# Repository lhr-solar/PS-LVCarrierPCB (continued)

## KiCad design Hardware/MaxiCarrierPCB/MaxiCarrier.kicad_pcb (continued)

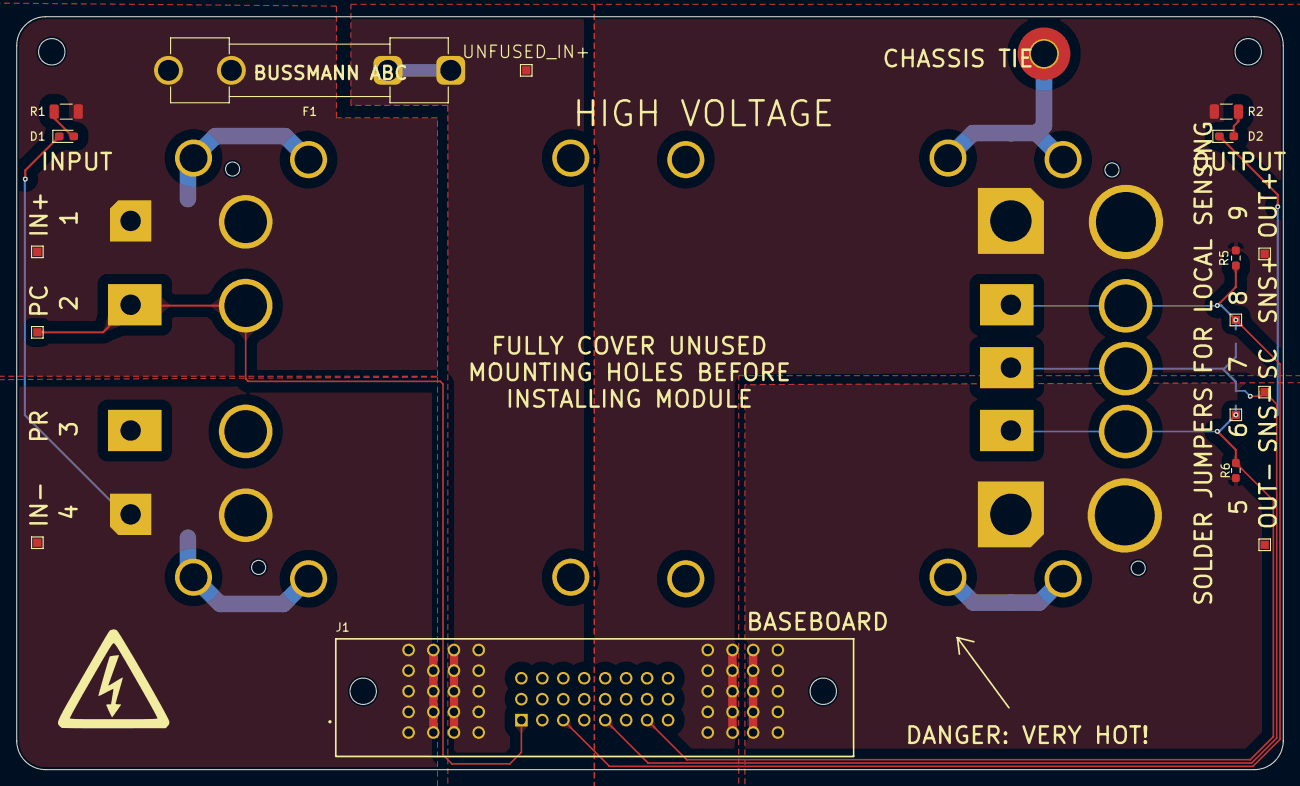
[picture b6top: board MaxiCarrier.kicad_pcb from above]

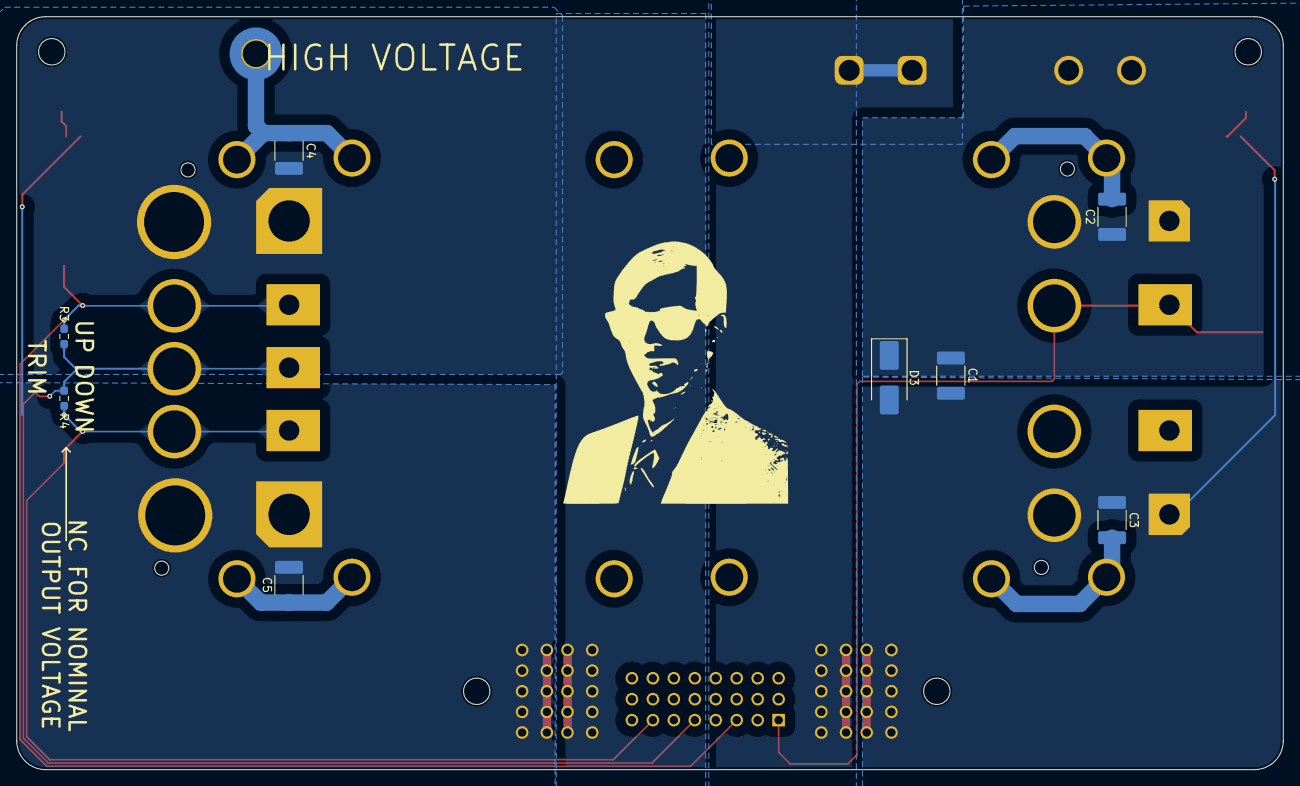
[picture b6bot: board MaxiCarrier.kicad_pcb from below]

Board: 2 copper layers, 153.5 x 91.2 mm, 31 parts (9 on the bottom side), 12 nets.

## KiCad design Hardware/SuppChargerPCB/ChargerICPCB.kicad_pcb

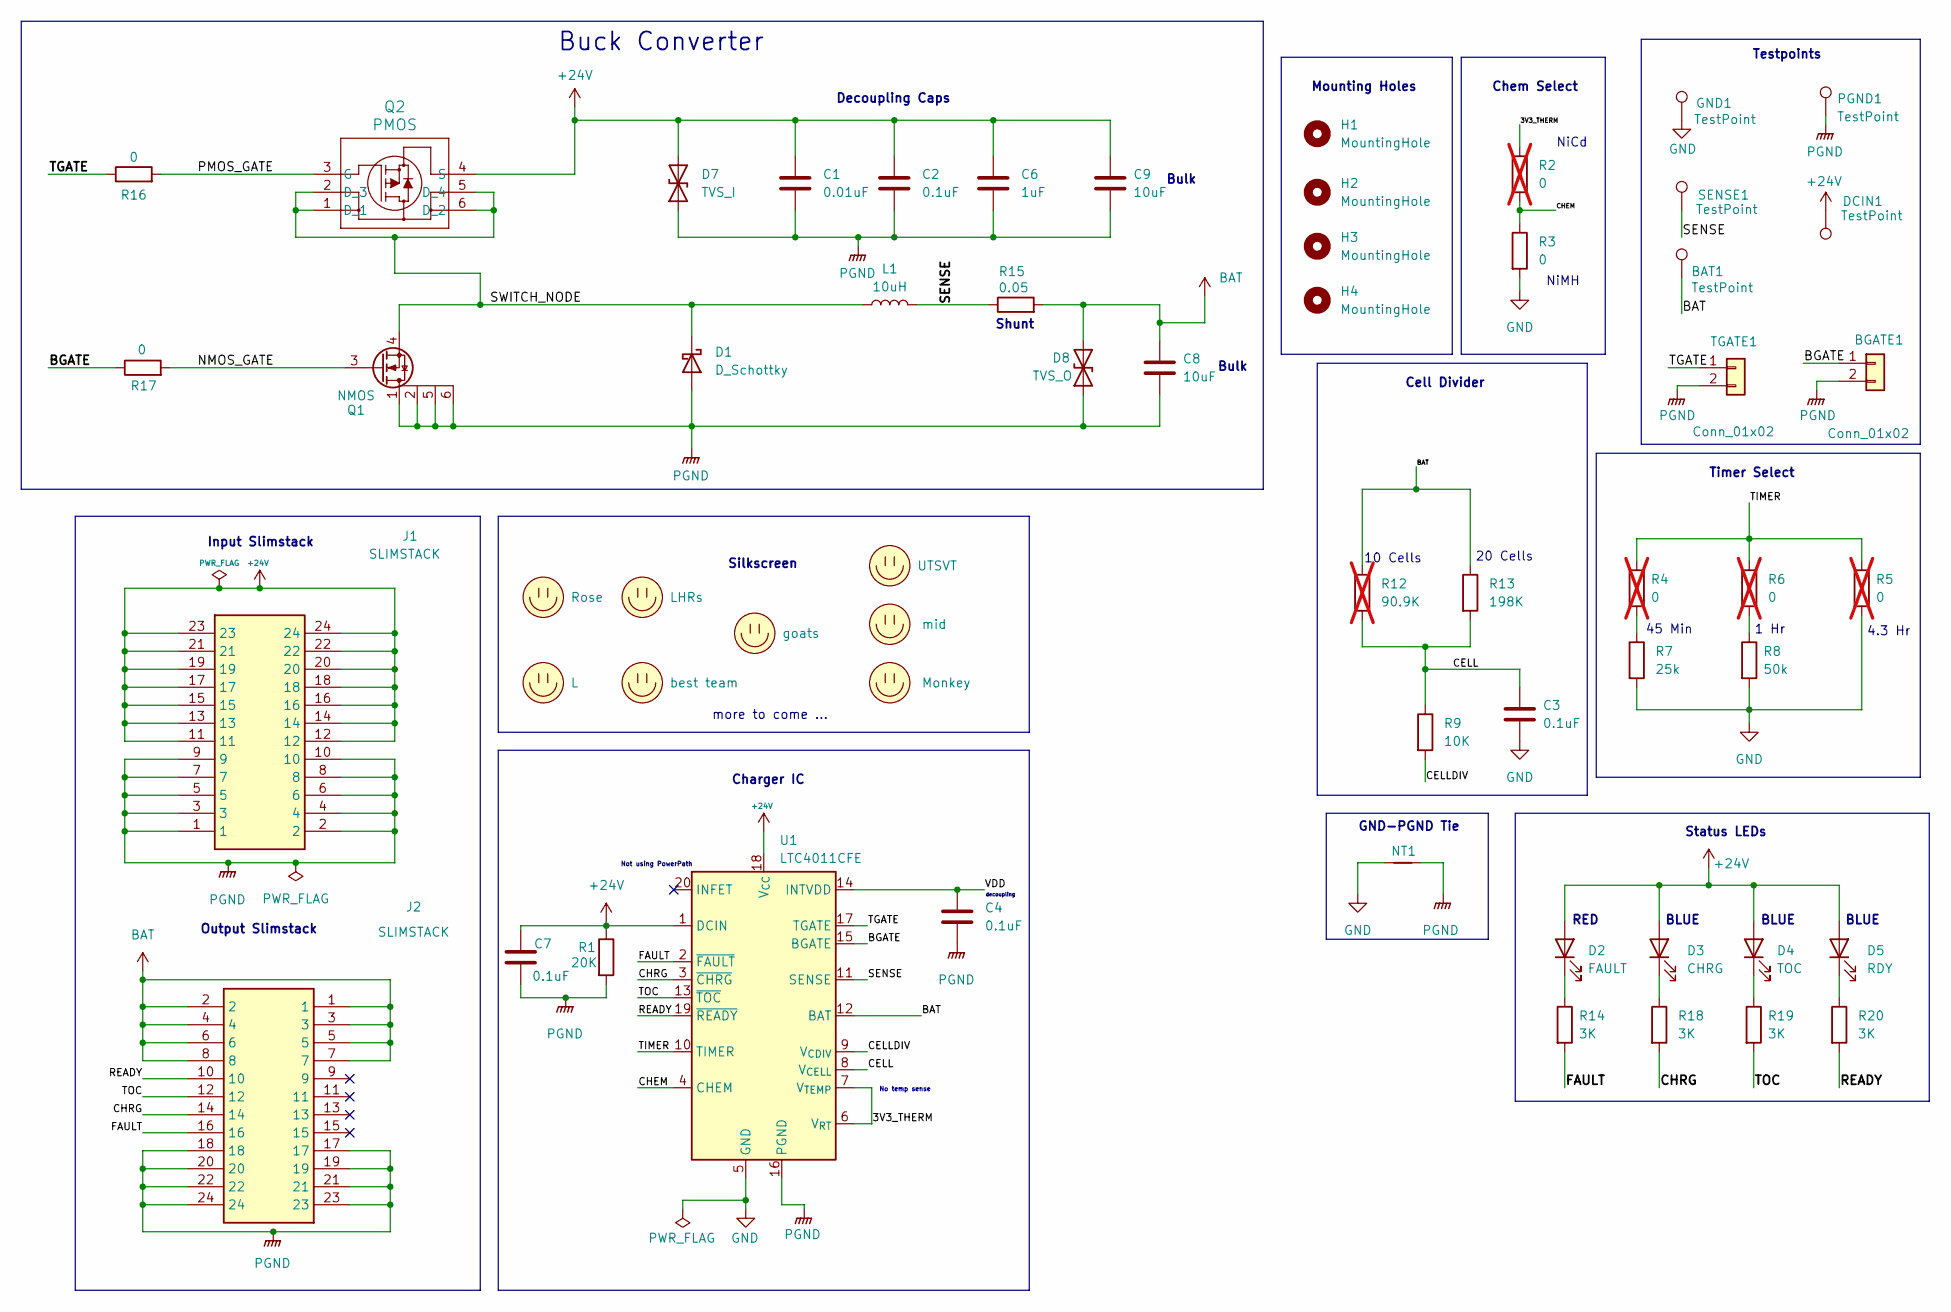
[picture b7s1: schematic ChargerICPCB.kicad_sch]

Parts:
BAT1: TestPoint; PinHeader_1x01_P2.54mm_Vertical
BGATE1: Conn_01x02; PinHeader_1x02_P2.54mm_Vertical
C1: 0.01uF; C_0603_1608Metric
C2, C3, C4, C7: 0.1uF; C_0603_1608Metric
C6: 1uF; C_0603_1608Metric
C8, C9: 10uF; C_0805_2012Metric
D1: D_Schottky; UPS140E3TR7
D2: FAULT; C_0603_1608Metric
D3: CHRG; LED_0603_1608Metric
D4: TOC; LED_0603_1608Metric
D5: RDY; LED_0603_1608Metric
D7: TVS_I; D_SMB
D8: TVS_O; D_SMB
DCIN1: TestPoint; PinHeader_1x01_P2.54mm_Vertical
GND1: TestPoint; PinHeader_1x01_P2.54mm_Vertical
H1, H2, H3, H4: MountingHole; MountingHole_3.2mm_M3
J1, J2: SLIMSTACK; 524652470; Mouser Part Number 538-52465-2470
L1: 10uH; WE-LHMI_7050
LOGO1: LHRs; LHRs_LOGO
LOGO2: UTSVT; UTSVT_Logo_Symbol
LOGO3: Monkey; monk
LOGO5: Rose; rose
LOGO6: L
LOGO7: best team; sunderland
LOGO8: goats; chinese
LOGO9: mid
NT1: NetTie_2; NetTie-2_SMD_Pad0.5mm
PGND1: TestPoint; PinHeader_1x01_P2.54mm_Vertical
Q1: NMOS; TSOP6_MO-193C_VIS; Mouser Part Number Si3456DDV
Q2: PMOS; TSOT23-6-419BL_OSI
R1: 20K; R_0603_1608Metric
R2, R4, R5, R6: 0; R_0603_1608Metric; not fitted
R3, R16, R17: 0; R_0603_1608Metric
R7: 25k; R_0603_1608Metric
R8: 50k; R_0603_1608Metric
R9: 10K; R_0603_1608Metric
R12: 90.9K; R_0603_1608Metric_Pad0.98x0.95mm_HandSolder; not fitted
R13: 198K; R_0603_1608Metric_Pad0.98x0.95mm_HandSolder
R14, R18, R19, R20: 3K; R_0603_1608Metric
R15: 0.05; R_0603_1608Metric
SENSE1: TestPoint; PinHeader_1x01_P2.54mm_Vertical
TGATE1: Conn_01x02; PinHeader_1x02_P2.54mm_Vertical
U1: LTC4011CFE; HTSSOP-20-1EP_4.4x6.5mm_P0.65mm_EP2.74x3.86mm

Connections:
+24V: C1.1, C2.1, C6.1, C7.1, C9.1, D2.2 (A), D3.2 (A), D4.2 (A), D5.2 (A), D7.2 (A2), DCIN1.1, J1.11, J1.12, J1.13, J1.14, J1.15, J1.16, J1.17, J1.18, J1.19, J1.20, J1.21, J1.22, J1.23, J1.24, Q2.4 (S), R1.1, U1.1 (DCIN), U1.18 (V_{CC})
/3V3_THERM: R2.1, U1.6 (V_{RT}), U1.7 (V_{TEMP})
/BGATE: BGATE1.1, R17.1, U1.15 (BGATE)
/CELL: C3.1, R9.1, R12.2, R13.2, U1.8 (V_{CELL})
/CELLDIV: R9.2, U1.9 (V_{CDIV})
/CHEM: R2.2, R3.1, U1.4 (CHEM)
/CHRG: J2.14, R18.2, U1.3 (~CHRG)
/FAULT: J2.16, R14.2, U1.2 (~FAULT)
/NMOS_GATE: Q1.3 (G), R17.2
/PMOS_GATE: Q2.3 (G), R16.2
/READY: J2.10, R20.2, U1.19 (~READY)
/SENSE: L1.2, R15.1, SENSE1.1, U1.11 (SENSE)
/SWITCH_NODE: D1.1 (K), L1.1, Q1.4 (S), Q2.1 (D_1), Q2.2 (D_3), Q2.5 (D_4), Q2.6 (D_2)
/TGATE: R16.1, TGATE1.1, U1.17 (TGATE)
/TIMER: R4.1, R5.1, R6.1, U1.10 (TIMER)
/TOC: J2.12, R19.2, U1.13 (~TOC)
/VDD: C4.1, U1.14 (INTVDD)
BAT: BAT1.1, C8.1, D8.2 (A2), J2.1, J2.2, J2.3, J2.4, J2.5, J2.6, J2.7, J2.8, R12.1, R13.1, R15.2, U1.12 (BAT)
GND: C3.2, GND1.1, NT1.1, R3.2, R5.2, R7.2, R8.2, U1.5 (GND), U1.21 (GND)
unnamed: D2.1 (K), R14.1
unnamed: D3.1 (K), R18.1
unnamed: D4.1 (K), R19.1
unnamed: D5.1 (K), R20.1
unnamed: R4.2, R7.1
unnamed: R6.2, R8.1
PGND: BGATE1.2, C1.2, C2.2, C4.2, C6.2, C7.2, C8.2, C9.2, D1.2 (A), D7.1 (A1), D8.1 (A1), J1.1, J1.2, J1.3, J1.4, J1.5, J1.6, J1.7, J1.8, J1.9, J1.10, J2.17, J2.18, J2.19, J2.20, J2.21, J2.22, J2.23, J2.24, NT1.2, PGND1.1, Q1.1 (D), Q1.2 (S), Q1.5 (S), Q1.6 (S), R1.2, TGATE1.2, U1.16 (PGND)

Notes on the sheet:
10 Cells
Shunt
4.3 Hr
decoupling
BLUE
RED
Status LEDs
Not using PowerPath
Silkscreen
Testpoints
GND-PGND Tie
Mounting Holes
Decoupling Caps
45 Min
Timer Select
Output Slimstack
more to come ...
20 Cells
Charger IC
No temp sense
Bulk
Cell Divider
NiMH
Buck Converter
NiCd
Input Slimstack
1 Hr
Chem Select

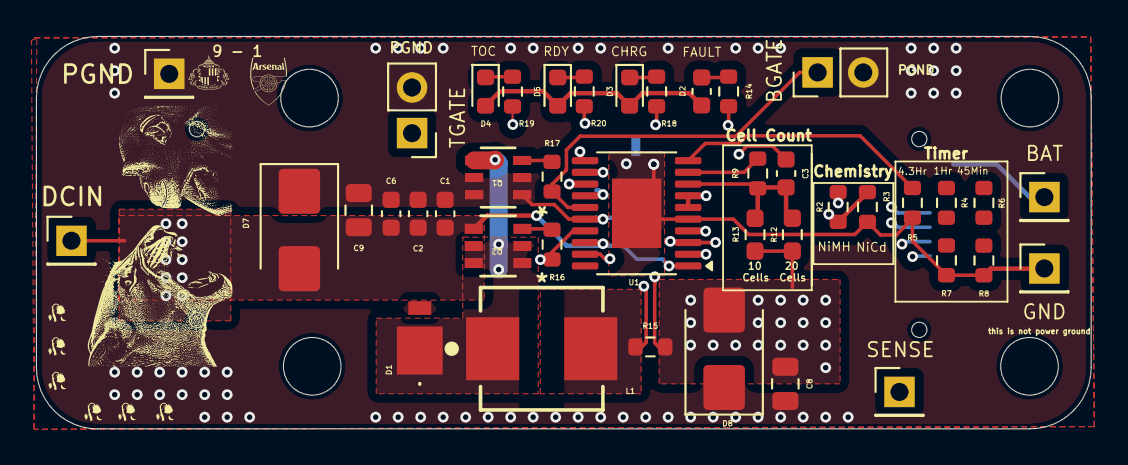
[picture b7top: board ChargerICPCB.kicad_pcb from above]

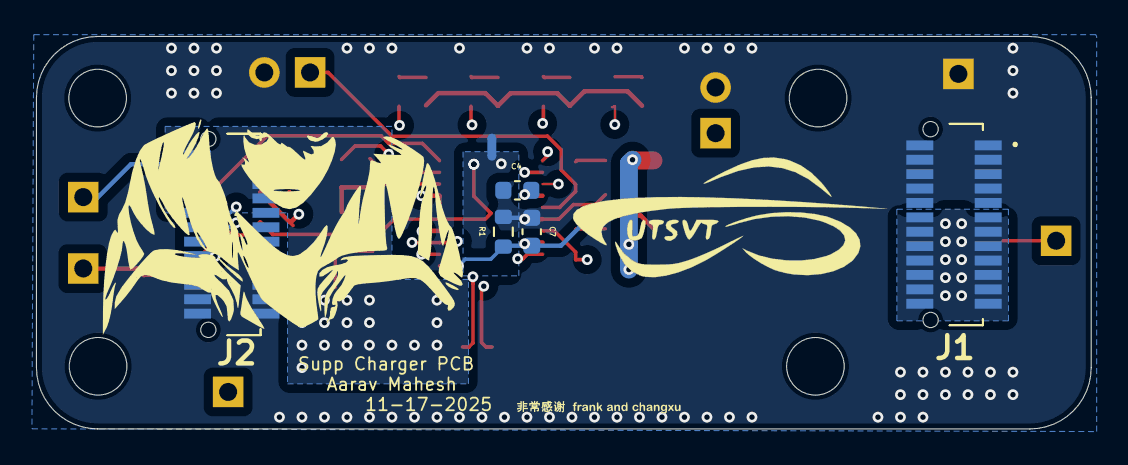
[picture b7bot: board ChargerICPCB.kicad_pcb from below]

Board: 4 copper layers, 58.6 x 21.8 mm, 64 parts (10 on the bottom side), 26 nets.

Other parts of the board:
LOGO5#2, LOGO5#3, LOGO5#4, LOGO5#5, LOGO5#6: Rose; rose

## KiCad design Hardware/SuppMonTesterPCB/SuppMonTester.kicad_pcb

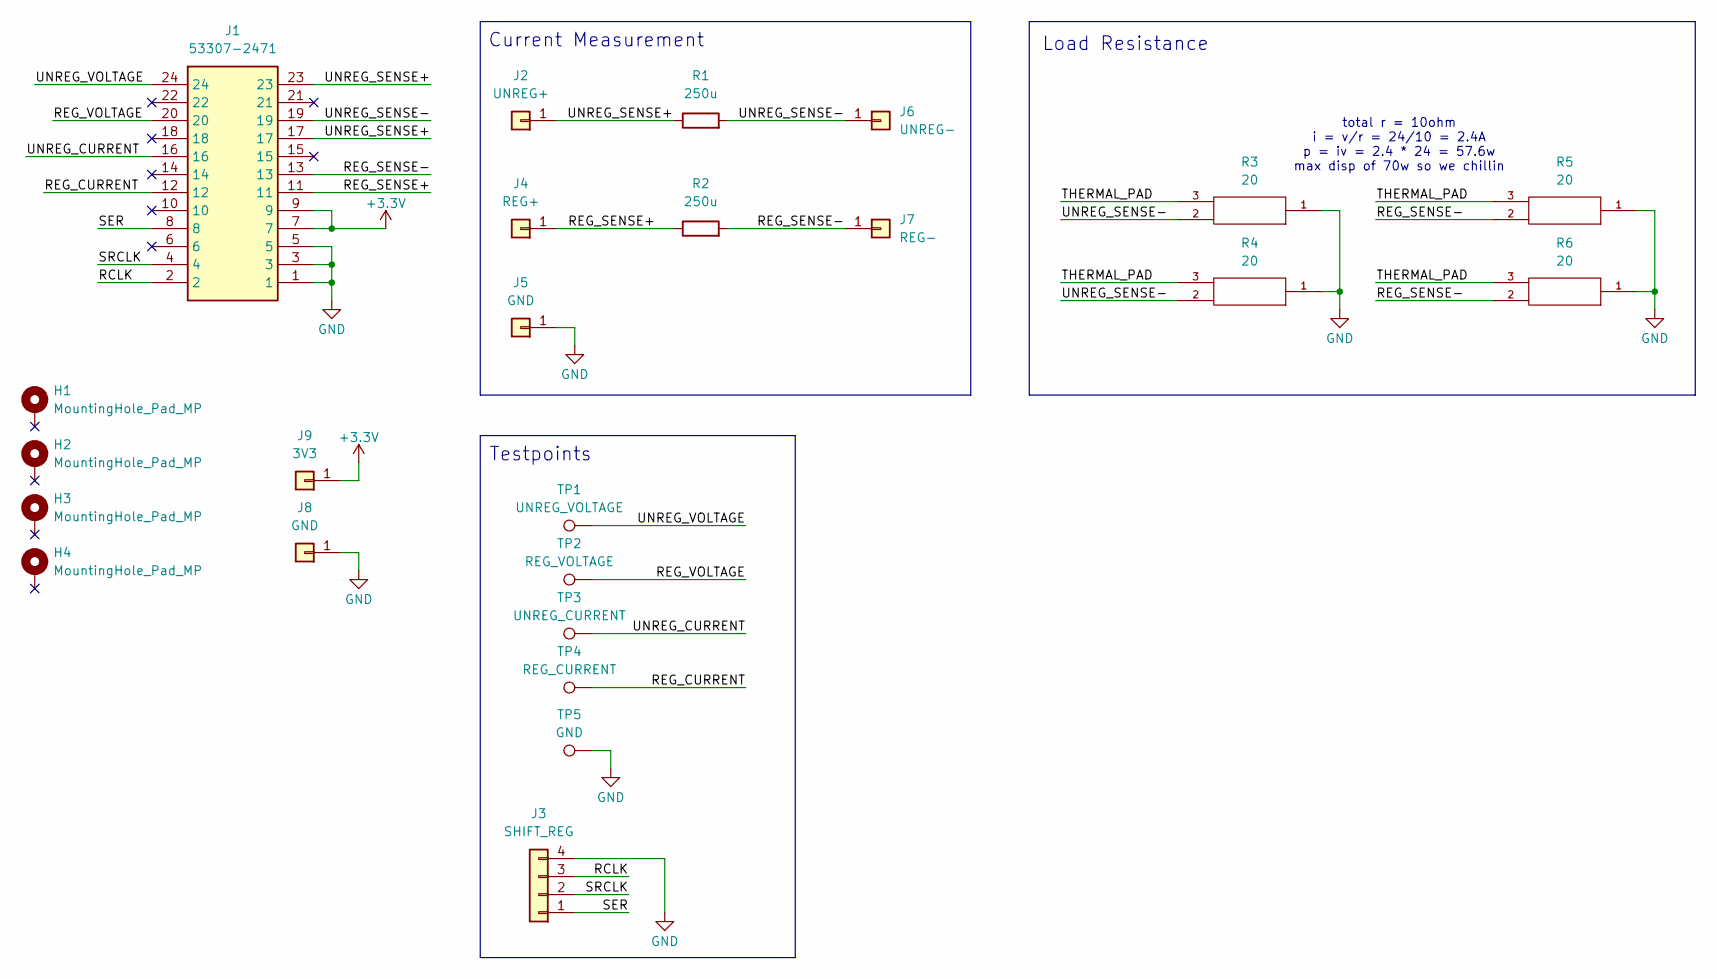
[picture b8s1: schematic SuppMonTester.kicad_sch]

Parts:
H1, H2, H3, H4: MountingHole_Pad_MP; MountingHole_3.2mm_M3_Pad
J1: 53307-2471; 533072471; Mouser Part Number 538-53307-2471
J2: UNREG+; 5754
J3: SHIFT_REG; PinHeader_1x04_P2.54mm_Vertical
J4: REG+; 5754
J5, J8: GND; 5754
J6: UNREG-; 5754
J7: REG-; 5754
J9: 3V3; 5754
R1, R2: 250u; R_1225_3264Metric_Pad1.47x6.45mm_HandSolder
R3, R4, R5, R6: 20; RES_PWR263S-35-3300F; PARTREV 12/20
TP1: UNREG_VOLTAGE; TestPoint_HEX_3mmID
TP2: REG_VOLTAGE; TestPoint_HEX_3mmID
TP3: UNREG_CURRENT; TestPoint_HEX_3mmID
TP4: REG_CURRENT; TestPoint_HEX_3mmID
TP5: GND; TestPoint_HEX_3mmID

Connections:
+3.3V: J1.7, J1.9, J9.1
/RCLK: J1.2, J3.3
/REG_CURRENT: J1.12, TP4.1
/REG_SENSE+: J1.11, J4.1, R2.1
/REG_SENSE-: J1.13, J7.1, R2.2, R5.2, R6.2
/REG_VOLTAGE: J1.20, TP2.1
/SER: J1.8, J3.1
/SRCLK: J1.4, J3.2
/THERMAL_PAD: R3.3, R4.3, R5.3, R6.3
/UNREG_CURRENT: J1.16, TP3.1
/UNREG_SENSE+: J1.17, J1.23, J2.1, R1.1
/UNREG_SENSE-: J1.19, J6.1, R1.2, R3.2, R4.2
/UNREG_VOLTAGE: J1.24, TP1.1
GND: J1.1, J1.3, J1.5, J3.4, J5.1, J8.1, R3.1, R4.1, R5.1, R6.1, TP5.1

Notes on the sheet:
total r = 10ohm i = v/r = 24/10 = 2.4A p = iv = 2.4 * 24 = 57.6w max disp of 70w so we chillin
Load Resistance
Current Measurement
Testpoints

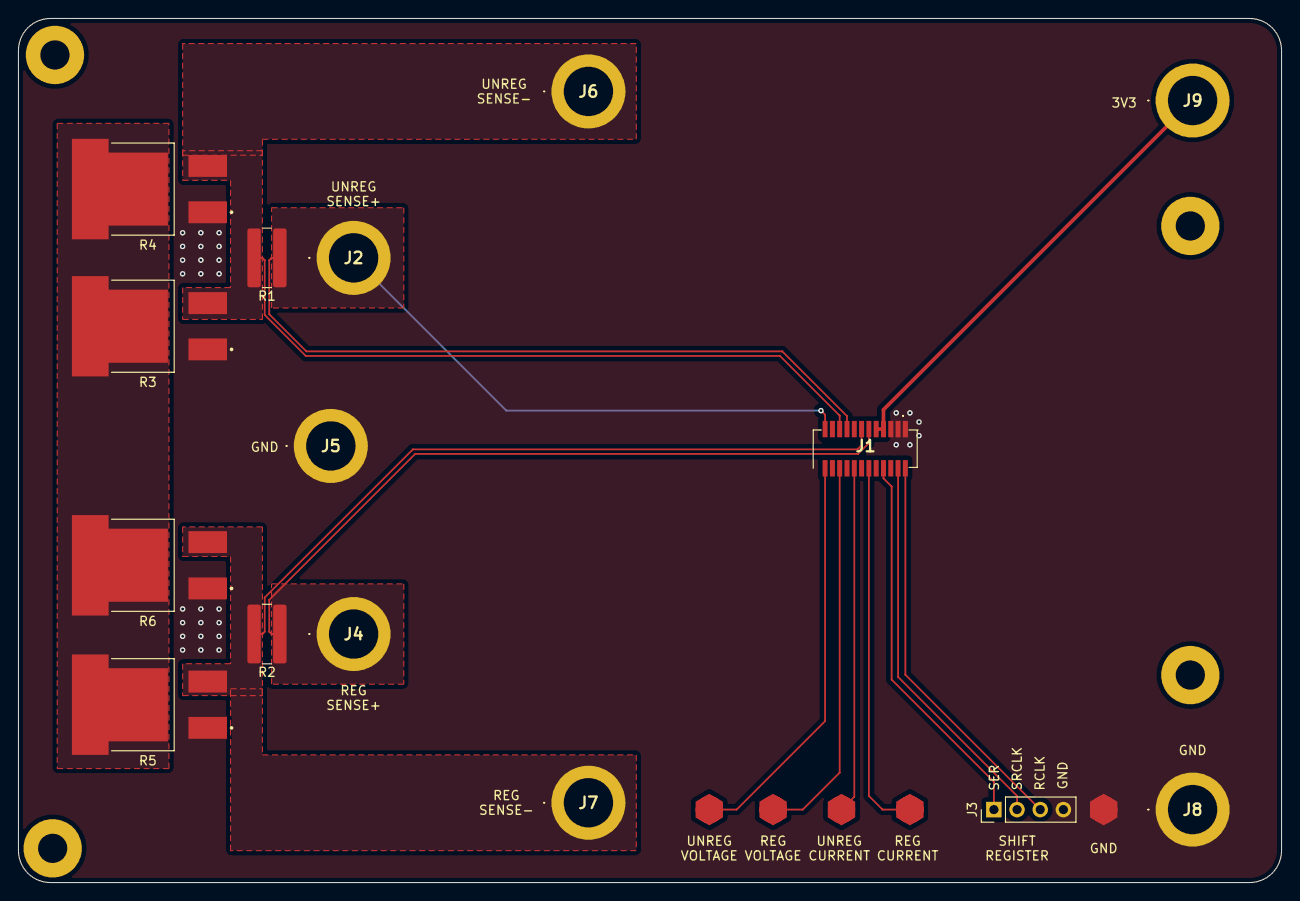
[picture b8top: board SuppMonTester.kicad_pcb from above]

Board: 2 copper layers, 138.5 x 94.8 mm, 24 parts (0 on the bottom side), 14 nets.

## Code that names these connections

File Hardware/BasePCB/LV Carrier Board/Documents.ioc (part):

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Mcu.Name=STM32G473R(B-C-E)Tx
Mcu.Package=LQFP64
Mcu.UserName=STM32G473RETx
PA0.GPIOParameters=GPIO_Label
PA0.GPIO_Label=R_Current
PA0.Mode=IN1-Single-Ended
PA0.Signal=ADC1_IN1
PA1.GPIOParameters=GPIO_Label
PA1.GPIO_Label=L_Current
PA1.Mode=IN2-Single-Ended
PA1.Signal=ADC2_IN2
PA10.GPIOParameters=GPIO_Label
PA10.GPIO_Label=UVR1
PA10.Signal=GPIO_Input
PA11.GPIOParameters=GPIO_Label
PA11.GPIO_Label=UVF2
PA11.Signal=GPIO_Input
PA12.GPIOParameters=GPIO_Label
PA12.GPIO_Label=UVF1
PA12.Signal=GPIO_Input
PA13.Mode=Serial_Wire
PA13.Signal=SYS_JTMS-SWDIO
PA14.Mode=Serial_Wire
PA14.Signal=SYS_JTCK-SWCLK
PA15.GPIOParameters=GPIO_Label
PA15.GPIO_Label=CANH
PA15.Mode=FDCAN_Activate
PA15.Signal=FDCAN3_TX
PA2.GPIOParameters=GPIO_Label
PA2.GPIO_Label=R_Voltage
PA2.Mode=IN3-Differential
PA2.Signal=ADC1_IN3
PA3.GPIOParameters=GPIO_Label
PA3.GPIO_Label=L_Voltage
PA3.Mode=IN3-Differential
PA3.Signal=ADC1_IN4
PA4.GPIOParameters=GPIO_Label
PA4.GPIO_Label=SD Card
PA4.Mode=NSS_Signal_Hard_Output
PA4.Signal=SPI1_NSS
PA5.GPIOParameters=GPIO_Label
PA5.GPIO_Label=SD Card
PA5.Mode=Full_Duplex_Master
PA5.Signal=SPI1_SCK
PA6.GPIOParameters=GPIO_Label
PA6.GPIO_Label=SD Card
PA6.Mode=Full_Duplex_Master
PA6.Signal=SPI1_MISO
PA7.GPIOParameters=GPIO_Label
PA7.GPIO_Label=SD Card
PA7.Mode=Full_Duplex_Master
PA7.Signal=SPI1_MOSI
PA8.GPIOParameters=GPIO_Label
PA8.GPIO_Label=CANL
PA8.Mode=FDCAN_Activate
PA8.Signal=FDCAN3_RX
PA9.GPIOParameters=GPIO_Label
PA9.GPIO_Label=SD Card Detect
PA9.Signal=GPIO_Input
PB0.GPIOParameters=GPIO_Label
PB0.GPIO_Label=CH1
PB0.Signal=GPIO_Input
PB1.GPIOParameters=GPIO_Label
PB1.GPIO_Label=L_Shunt
PB1.Mode=IN12-Single-Ended
PB1.Signal=ADC1_IN12
PB10.GPIOParameters=GPIO_Label
PB10.GPIO_Label=UVR2
PB10.Signal=GPIO_Input
PB11.GPIOParameters=GPIO_Label
PB11.GPIO_Label=SUPP V out
PB11.Signal=GPIO_Input
PB12.GPIOParameters=GPIO_Label
PB12.GPIO_Label=VALID2
PB12.Signal=GPIO_Input
PB13.GPIOParameters=GPIO_Label
PB13.GPIO_Label=FTL2
PB13.Signal=GPIO_Output
PB14.GPIOParameters=GPIO_Label
PB14.GPIO_Label=FTL1
PB14.Signal=GPIO_Output
PB15.GPIOParameters=GPIO_Label
PB15.GPIO_Label=CHL2
PB15.Signal=GPIO_Output
PB2.GPIOParameters=GPIO_Label
PB2.GPIO_Label=FAULT1
PB2.Signal=GPIO_Input
PB3.GPIOParameters=GPIO_Label
PB3.GPIO_Label=OV1
PB3.Signal=GPIO_Input
PB4.GPIOParameters=GPIO_Label
PB4.GPIO_Label=STATUS_LED
PB4.Mode=PWM Generation2 CH2N
PB4.Signal=TIM8_CH2N
PB5.GPIOParameters=GPIO_Label
PB5.GPIO_Label=SR_CLK
PB5.Signal=S_TIM17_CH1
PB6.Signal=S_TIM8_CH1
PB7.GPIOParameters=GPIO_Label
PB7.GPIO_Label=BOOT Switch
PB7.Signal=GPIO_Input
PB8-BOOT0.GPIOParameters=GPIO_Label
PB8-BOOT0.GPIO_Label=BootSwitch
PB8-BOOT0.Signal=GPIO_Input
PB9.GPIOParameters=GPIO_Label
PB9.GPIO_Label=SR_Data
PB9.Signal=GPIO_Input
PC0.GPIOParameters=GPIO_Label
PC0.GPIO_Label=R_Input
PC0.Mode=IN6-Differential
PC0.Signal=ADC1_IN6
PC1.GPIOParameters=GPIO_Label
PC1.GPIO_Label=L_Input
PC1.Mode=IN6-Differential
PC1.Signal=ADC1_IN7
PC10.GPIOParameters=GPIO_Label
PC10.GPIO_Label=Supp V Out
PC10.Signal=GPIO_Input
PC11.GPIOParameters=GPIO_Label
PC11.GPIO_Label=DISABLE2
PC11.Signal=GPIO_Input
PC12.GPIOParameters=GPIO_Label
PC12.GPIO_Label=VALID1
PC12.Signal=GPIO_Input
PC13.GPIOParameters=GPIO_Label
PC13.GPIO_Label=CH1
PC13.Signal=GPIO_Input
PC14-OSC32_IN.GPIOParameters=GPIO_Label
PC14-OSC32_IN.GPIO_Label=FAULT2
PC14-OSC32_IN.Signal=GPIO_Input
PC15-OSC32_OUT.GPIOParameters=GPIO_Label
PC15-OSC32_OUT.GPIO_Label=CH2
PC15-OSC32_OUT.Signal=GPIO_Input
PC2.GPIOParameters=GPIO_Label
PC2.GPIO_Label=R_Shunt
PC2.Mode=IN8-Differential
PC2.Signal=ADC1_IN8
PC3.GPIOParameters=GPIO_Label
PC3.GPIO_Label=IMON
PC3.Mode=IN8-Differential
PC3.Signal=ADC1_IN9
PC4.Mode=Asynchronous
PC4.Signal=USART1_TX
PC5.Mode=Asynchronous
PC5.Signal=USART1_RX
PC6.GPIOParameters=GPIO_Label
PC6.GPIO_Label=CHL1
PC6.Signal=GPIO_Output
PC7.GPIOParameters=GPIO_Label
PC7.GPIO_Label=VDL2
PC7.Signal=GPIO_Output
PC8.GPIOParameters=GPIO_Label
PC8.GPIO_Label=VDL1
PC8.Signal=GPIO_Output
PC9.GPIOParameters=GPIO_Label
PC9.GPIO_Label=OV2
PC9.Signal=GPIO_Input
PD2.GPIOParameters=GPIO_Label
PD2.GPIO_Label=DISABLE1
PD2.Signal=GPIO_Input
PF0-OSC_IN.GPIOParameters=GPIO_Label
PF0-OSC_IN.GPIO_Label=Crystal
PF0-OSC_IN.Mode=HSE-External-Oscillator
PF0-OSC_IN.Signal=RCC_OSC_IN
PF1-OSC_OUT.GPIOParameters=GPIO_Label
PF1-OSC_OUT.GPIO_Label=Crystal
PF1-OSC_OUT.Mode=HSE-External-Oscillator
PF1-OSC_OUT.Signal=RCC_OSC_OUT
PG10-NRST.GPIOParameters=GPIO_Label
PG10-NRST.GPIO_Label=Reset Button
PG10-NRST.Signal=GPIO_Input
RCC.HSE_VALUE=8000000
RCC.SYSCLKFreq_VALUE=16000000
board=custom

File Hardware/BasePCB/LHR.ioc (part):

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Mcu.Name=STM32G473R(B-C-E)Tx
Mcu.Package=LQFP64
Mcu.UserName=STM32G473RETx
PA0.GPIOParameters=GPIO_Label
PA0.GPIO_Label=SUPPMON_V2
PA0.Signal=ADC1_IN1
PA1.GPIOParameters=GPIO_Label
PA1.GPIO_Label=SUPPMON_V1
PA1.Mode=IN2-Differential
PA1.Signal=ADC1_IN2
PA10.GPIOParameters=GPIO_Label
PA10.GPIO_Label=SR_CLK
PA10.Signal=S_TIM1_CH3
PA13.Signal=SYS_JTMS-SWDIO
PA14.Signal=SYS_JTCK-SWCLK
PA15.GPIOParameters=GPIO_Label
PA15.GPIO_Label=CAN_H
PA15.Mode=FDCAN_Activate
PA15.Signal=FDCAN3_TX
PA2.GPIOParameters=GPIO_Label
PA2.GPIO_Label=SUPPMON_I1
PA2.Mode=IN2-Differential
PA2.Signal=ADC1_IN3
PA4.GPIOParameters=GPIO_Label
PA4.GPIO_Label=SDCARD
PA4.Signal=SPI1_NSS
PA5.GPIOParameters=GPIO_Label
PA5.GPIO_Label=SDCARD
PA5.Signal=SPI1_SCK
PA6.GPIOParameters=GPIO_Label
PA6.GPIO_Label=SDCARD
PA6.Signal=SPI1_MISO
PA7.GPIOParameters=GPIO_Label
PA7.GPIO_Label=SDCARD
PA7.Signal=SPI1_MOSI
PA8.GPIOParameters=GPIO_Label
PA8.GPIO_Label=CAN_L
PA8.Mode=FDCAN_Activate
PA8.Signal=FDCAN3_RX
PA9.GPIOParameters=GPIO_Label
PA9.GPIO_Label=SDCARD_Detect
PA9.Signal=GPIO_Input
PB11.GPIOParameters=GPIO_Label
PB11.GPIO_Label=CHL1
PB11.Signal=GPIO_Input
PB12.GPIOParameters=GPIO_Label
PB12.GPIO_Label=CHL2
PB12.Signal=GPIO_Input
PB13.Signal=GPIO_Output
PB14.GPIOParameters=GPIO_Label
PB14.GPIO_Label=FTL2
PB14.Signal=GPIO_Input
PB15.GPIOParameters=GPIO_Label
PB15.GPIO_Label=VDL1
PB15.Signal=GPIO_Input
PB3.GPIOParameters=GPIO_Label
PB3.GPIO_Label=Status_Led
PB3.Signal=S_TIM2_CH2
PB4.GPIOParameters=GPIO_Label
PB4.GPIO_Label=DISABLE1
PB4.Signal=GPIO_Input
PB5.GPIOParameters=GPIO_Label
PB5.GPIO_Label=SR_Data
PB5.Signal=GPIO_Output
PB6.GPIOParameters=GPIO_Label
PB6.GPIO_Label=LED_Addressable
PB6.Signal=S_TIM8_CH1
PB7.GPIOParameters=GPIO_Label
PB7.GPIO_Label=BOOT_Switch
PB7.Signal=GPIO_Input
PB8-BOOT0.GPIOParameters=GPIO_Label
PB8-BOOT0.GPIO_Label=BOOT_Switch
PB8-BOOT0.Signal=GPIO_Input
PB9.GPIOParameters=GPIO_Label
PB9.GPIO_Label=VDL2
PB9.Signal=GPIO_Input
PC1.GPIOParameters=GPIO_Label
PC1.GPIO_Label=SUPPMON_I2
PC1.Signal=ADC1_IN7
PC10.GPIOParameters=GPIO_Label
PC10.GPIO_Label=SHDN
PC10.Signal=GPIO_Input
PC11.GPIOParameters=GPIO_Label
PC11.GPIO_Label=DISABLE2
PC11.Signal=GPIO_Input
PC12.GPIOParameters=GPIO_Label
PC12.GPIO_Label=USB_UART
PC12.Signal=UART5_TX
PC3.GPIOParameters=GPIO_Label
PC3.GPIO_Label=IMON
PC3.Signal=OPAMP5_VINP
PD2.GPIOParameters=GPIO_Label
PD2.GPIO_Label=USB_UART
PD2.Signal=UART5_RX
PF0-OSC_IN.GPIOParameters=GPIO_Label
PF0-OSC_IN.GPIO_Label=Crystal
PF0-OSC_IN.Mode=HSE-External-Oscillator
PF0-OSC_IN.Signal=RCC_OSC_IN
PF1-OSC_OUT.GPIOParameters=GPIO_Label
PF1-OSC_OUT.GPIO_Label=Crystal
PF1-OSC_OUT.Mode=HSE-External-Oscillator
PF1-OSC_OUT.Signal=RCC_OSC_OUT
PG10-NRST.GPIOParameters=GPIO_Label
PG10-NRST.GPIO_Label=Reset_BTN
PG10-NRST.Signal=GPIO_Input
RCC.HSE_VALUE=8000000
RCC.SYSCLKFreq_VALUE=16000000
board=custom

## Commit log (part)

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2025-12-06 schematic
2025-12-06 schematic changes
2025-12-14 update KiCAD sharepoint
2025-12-14 Maxi Carrier Symbol/Footprint/PCB (#2)
    * test
    * initial dc-dc sch
    * more sch + some footprints
    * holy fatass
    * hehehhe
    * done?
2025-12-14 LV Mux Hat Rev A (#1)
    * test
    * Added PSOM pins and LEDS fixed the resistors for 24V remove SHDN logic
    * added the lib!
    * remake pt things missing 1. R values SHDN Logic
    * updated sch
    * updated sch added new footprints
2025-12-14 fixed some shi
2025-12-14 donut daddy
2025-12-14 gerbs
2025-12-14 change OV and fix silk
2025-12-14 fix the chinese man
2025-12-14 negative logic switches fix
2025-12-14 final baby lfg
2025-12-14 bom 2
2025-12-14 gerbs again
2025-12-14 updated step file
2025-12-14 lakshya gupta
2025-12-15 LV Base Git Cleanup (#15)
    * Maxi Carrier Symbol/Footprint/PCB (#2)
    * test
    * initial dc-dc sch
    * more sch + some footprints
    * holy fatass
    * hehehhe
2025-12-15 started code
2025-12-16 openocd stuff
2025-12-16 add Sharepoint
2025-12-16 cleaned up power mux
2025-12-16 powa mux
2025-12-17 fix basePCB libs
2025-12-17 fix suppmon tester
2025-12-17 2 Layer Maxi Carrier (#17)
    * started 2 layer layout
    * Finished 2 layer layout
    * Removed plate connections
    * Fixed some traces
    * round
    ---------
2025-12-17 stuff
2025-12-17 Symbol & Footprint Library Cleanup (#16)
    * cleaned up power mux
    * powa mux
    * fix basePCB libs
    * fix suppmon tester
    * stuff
2025-12-17 remove suppmontester submodule
2025-12-20 add hall effect sensor
2025-12-20 add LPF to ADC inputs
2025-12-21 schem done?
2025-12-21 supp charger routing done
2025-12-21 swap stat pins in supp charger
2025-12-21 cleanup a few stray traces
2025-12-21 reorg
2025-12-22 supp bat hall effect routing
2025-12-22 adc lpf routing and layout
2025-12-23 only 4 traces left
2025-12-23 everything connected
2025-12-23 silk + panda
2025-12-23 minor silk changes
2025-12-23 align things
2025-12-24 add JLC p/n
2025-12-25 lil shah part 1
2025-12-26 need to add connector symbols, desmos
2025-12-27 new hall effect IC
2025-12-27 lil shah pt 2
2025-12-27 added calcs, logic analyzer
2025-12-27 lil shah pt 3
2025-12-27 need to assign bulk cap
2025-12-27 abused pwr flags
2025-12-28 lil shah pt 3.5
2025-12-30 remove not needed kicad schematic sheet
2025-12-31 pre sheet reorg
2025-12-31 lakshay comments
2025-12-31 halo
2026-01-02 stared adding jlcpcb p/ns
2026-01-03 3d mods
2026-01-04 a layout
2026-01-04 use kicad sharepoint NVFM symbol
2026-01-07 mostly done w/ rev b
2026-01-07 revert powermux changes accidentally pushed
2026-01-07 update design spreadsheet
2026-01-08 update ov and uv resistors
2026-01-08 f a t pikachu
2026-01-09 fix pmos symbol
2026-01-09 updated sharepoint
2026-01-09 womp womop
2026-01-09 lv carrier jlc p/n
2026-01-09 sizing for base
2026-01-09 slightly higher
2026-01-10 fixed edge cut
2026-01-10 frank
2026-01-10 changed supp charger to new footprint
2026-01-10 greg heffley
2026-01-10 need to route signal
2026-01-10 most prod files
2026-01-10 aloha
2026-01-11 updated prod files
2026-01-11 added leds
2026-01-12 PowerMux Rev B (#19)
    * stared adding jlcpcb p/ns
    * mostly done w/ rev b
    * stuff
    * update design spreadsheet
    * update ov and uv resistors
    * f a t pikachu
2026-01-12 update lvmux 3d model
2026-01-12 two tps
2026-01-13 big boy shunt
2026-01-13 layout
2026-01-14 BOM again
2026-01-14 add supp charger 3d model
2026-01-14 fck u lil shah
2026-01-14 rm numbers
2026-01-14 le board is ordered
2026-01-14 LV Base Rev B (#18)
    * add hall effect sensor
    * add LPF to ADC inputs
    * schem done?
    * supp charger routing done
    * swap stat pins in supp charger
    * cleanup a few stray traces
2026-01-14 lakman
2026-01-15 bagel
2026-01-15 restored supp mon
2026-01-15 firmware
2026-01-15 remove not needed component files
2026-01-15 remove diff eda software files
2026-01-17 Firmware setup (#20)
    * firmware
    * stuff
2026-01-23 lv mux test board
2026-01-23 lv mux test board (#21)
2026-01-23 remove purple stuff
2026-01-23 Supp Charger PCB (#12)
    * schematic
    * reorg
    * need to add connector symbols, desmos
    * added calcs, logic analyzer
    * need to assign bulk cap
    * abused pwr flags
2026-01-23 ok (#22)
2026-01-31 lv-mux led test code 1
2026-01-31 more gpio
2026-01-31 Driver stuff
2026-02-06 added output log
2026-02-06 driver
2026-02-09 started cli
2026-02-09 add lut python scripts
2026-02-10 shdn testing on the board
2026-02-10 fix workflow and gpio driver
2026-02-10 acks
2026-02-10 build fix
2026-02-10 add status led driver
2026-02-10 wrote more bs gpio wrappers
2026-02-12 kell a bum
2026-02-13 LV enable
2026-02-14 test code
2026-02-14 code
2026-02-17 fuckass thread pool
2026-02-17 sum valid i2c
2026-02-18 stupid gemini comments
2026-02-18 Board Bringup (#26)
    * started cli
    * add lut python scripts
    * :(
    * shdn testing on the board
    * fix workflow and gpio driver
    * build fix
2026-02-21 ltc testing
2026-02-21 balls
2026-02-21 poop
2026-02-24 started funny adc logic
2026-02-24 most of fault state done
2026-02-24 better test
2026-02-24 finished test
2026-02-24 comments :0
2026-02-25 holy cook
2026-02-25 gemini might be cooking a lil
2026-02-25 some dumb code review stuff
2026-02-25 faults but some weird shit is happening
2026-02-25 whoopsie doopsie
2026-02-25 whoopsie doopsie (#31)
2026-02-25 remove fault hook
2026-02-25 standardize naming
2026-02-26 mostly done (no work)
2026-02-26 can read voltages
2026-02-26 adc reads, conversion no work :(
2026-02-26 timers :p
2026-02-27 suppmon rev c schem done
2026-02-27 schm actually done now whoops
2026-02-27 gemini ignore
2026-02-27 add pullup for SRCLR
2026-02-27 seven segment routing
2026-02-28 routing mostly done
2026-02-28 hall adc lut fix
2026-02-28 y does ts not work
2026-02-28 make one queue size
2026-02-28 charges litech
2026-03-01 workday testing
2026-03-01 board done and in cart
2026-03-01 should b good
2026-03-02 little shah
2026-03-02 freertos reorg
2026-03-02 Fault State (#30)
    * most of fault state done
    * better test
    * finished test
    * comments :0
    * holy cook
    * gemini might be cooking a lil
2026-03-02 ltc hotfixes
2026-03-02 move supp charger to adc3
2026-03-02 fixed 24v
2026-03-02 ordered
2026-03-02 Supp mon Rev C (#33)
    * suppmon rev c schem done
    * schm actually done now whoops
    * gemini ignore
    * add pullup for SRCLR
    * seven segment routing
    * routing mostly done
2026-03-02 fault bitmaps worky
2026-03-02 fault task
2026-03-02 review ts
2026-03-02 Ltc4421 Driver (#28)
    * ltc testing
    * balls
    * poop
    * ltc hotfixes
2026-03-03 ignore
2026-03-04 balls (#37)
2026-03-04 Supp Charger Rev B (#34)
    * should b good
    * fixed 24v
2026-03-05 port over nvic code soon
2026-03-05 okur
2026-03-05 fix workflow i think
2026-03-06 hit ev but not i2c callbacks
2026-03-06 hits tx and rx
2026-03-06 aint charging
2026-03-07 semphr in error callback
2026-03-07 prereq bits :)
2026-03-07 works?
2026-03-07 works, weird power on
2026-03-08 workday
2026-03-11 check diffs
2026-03-11 addressed some
2026-03-11 comments left
2026-03-11 save
2026-03-11 q set
2026-03-12 send once
2026-03-13 whole lotta red
2026-03-13 hurro
2026-03-14 ybg don
2026-03-14 main
2026-03-20 agnosticism
2026-03-20 hola
2026-03-20 lv carrer step
2026-03-20 lv carrier step update (#38)
2026-03-24 update suppmon symbol with updated 3d model
2026-03-24 add rendered steps
2026-03-24 lv mux rendered step
2026-03-24 fat steps
2026-03-24 rendered leadersom
2026-03-26 tuffest driver since readcarcan
2026-03-26 felize navidad
2026-03-26 halal
2026-03-26 mack-crow
2026-03-28 Supp Charger Firmware (#36)
    * acks
    * kell a bum
    * fuckass thread pool
    * sum valid i2c
    * wya
    * y does ts not work
2026-03-28 Rendered steps (#39)
    * add rendered steps
    * lv mux rendered step
    * fat steps
    * rendered leadersom
    * balls
2026-03-28 wrote canbus driver
2026-03-28 add canbus test
2026-03-28 add car can msgs in
2026-03-28 bleh
2026-03-28 add comments
2026-03-28 init tx header first
2026-03-28 add suppCharger thread
2026-03-28 update voltage conversion ratio
2026-03-29 work
2026-03-31 dw about how i deleted voltage sense
2026-04-03 pinout right now
2026-04-03 seeing msges on car can l
2026-04-04 ibat
2026-04-04 works w/ external loopbak
2026-04-04 peak dont ack
2026-04-04 new car can
2026-04-04 Canbus driver (#40)
    * wrote canbus driver
    * add canbus test
    * add car can msgs in
    * bleh
    * add comments
    * init tx header first
2026-04-04 ADC Driver (#32)
    * started funny adc logic
    * mostly done (no work)
    * can read voltages
    * adc reads, conversion no work :(
    * timers :p
    * hall adc lut fix
2026-04-04 new pins
2026-04-09 can restart charging without power ycle
2026-04-09 testing ibat
2026-04-10 i speak for the trees
2026-04-10 charge current slightly finnicky
2026-04-16 balls 2
2026-04-17 can msgs send succesfully
2026-04-17 fix frame ID
2026-04-17 code for power mux thread
2026-04-18 add power mux monitor can packing
2026-04-18 supp batt voltage works, supp reg does not :(
2026-04-20 supp charger thread overhall
2026-04-20 mr. mahesh
2026-04-20 aarav mahesh from akash academy
2026-04-20 lakshay gupta from aakash academy
2026-04-20 limit sanitzation
2026-04-21 bitmask fix
2026-04-24 fix my oopsie
2026-04-25 fix some jlc p/n's
2026-04-25 can code for charger, not in thread
2026-04-30 actual prod files
2026-04-30 Rev C Carrier (#42)
    * balls
    * balls
    * fix some jlc p/n's
    * balls
    * balls
    * actual prod files
2026-05-02 new NMOS RevX Design
2026-05-02 add KiCad sharepoint files
2026-05-02 updated p/n
2026-05-05 chud
